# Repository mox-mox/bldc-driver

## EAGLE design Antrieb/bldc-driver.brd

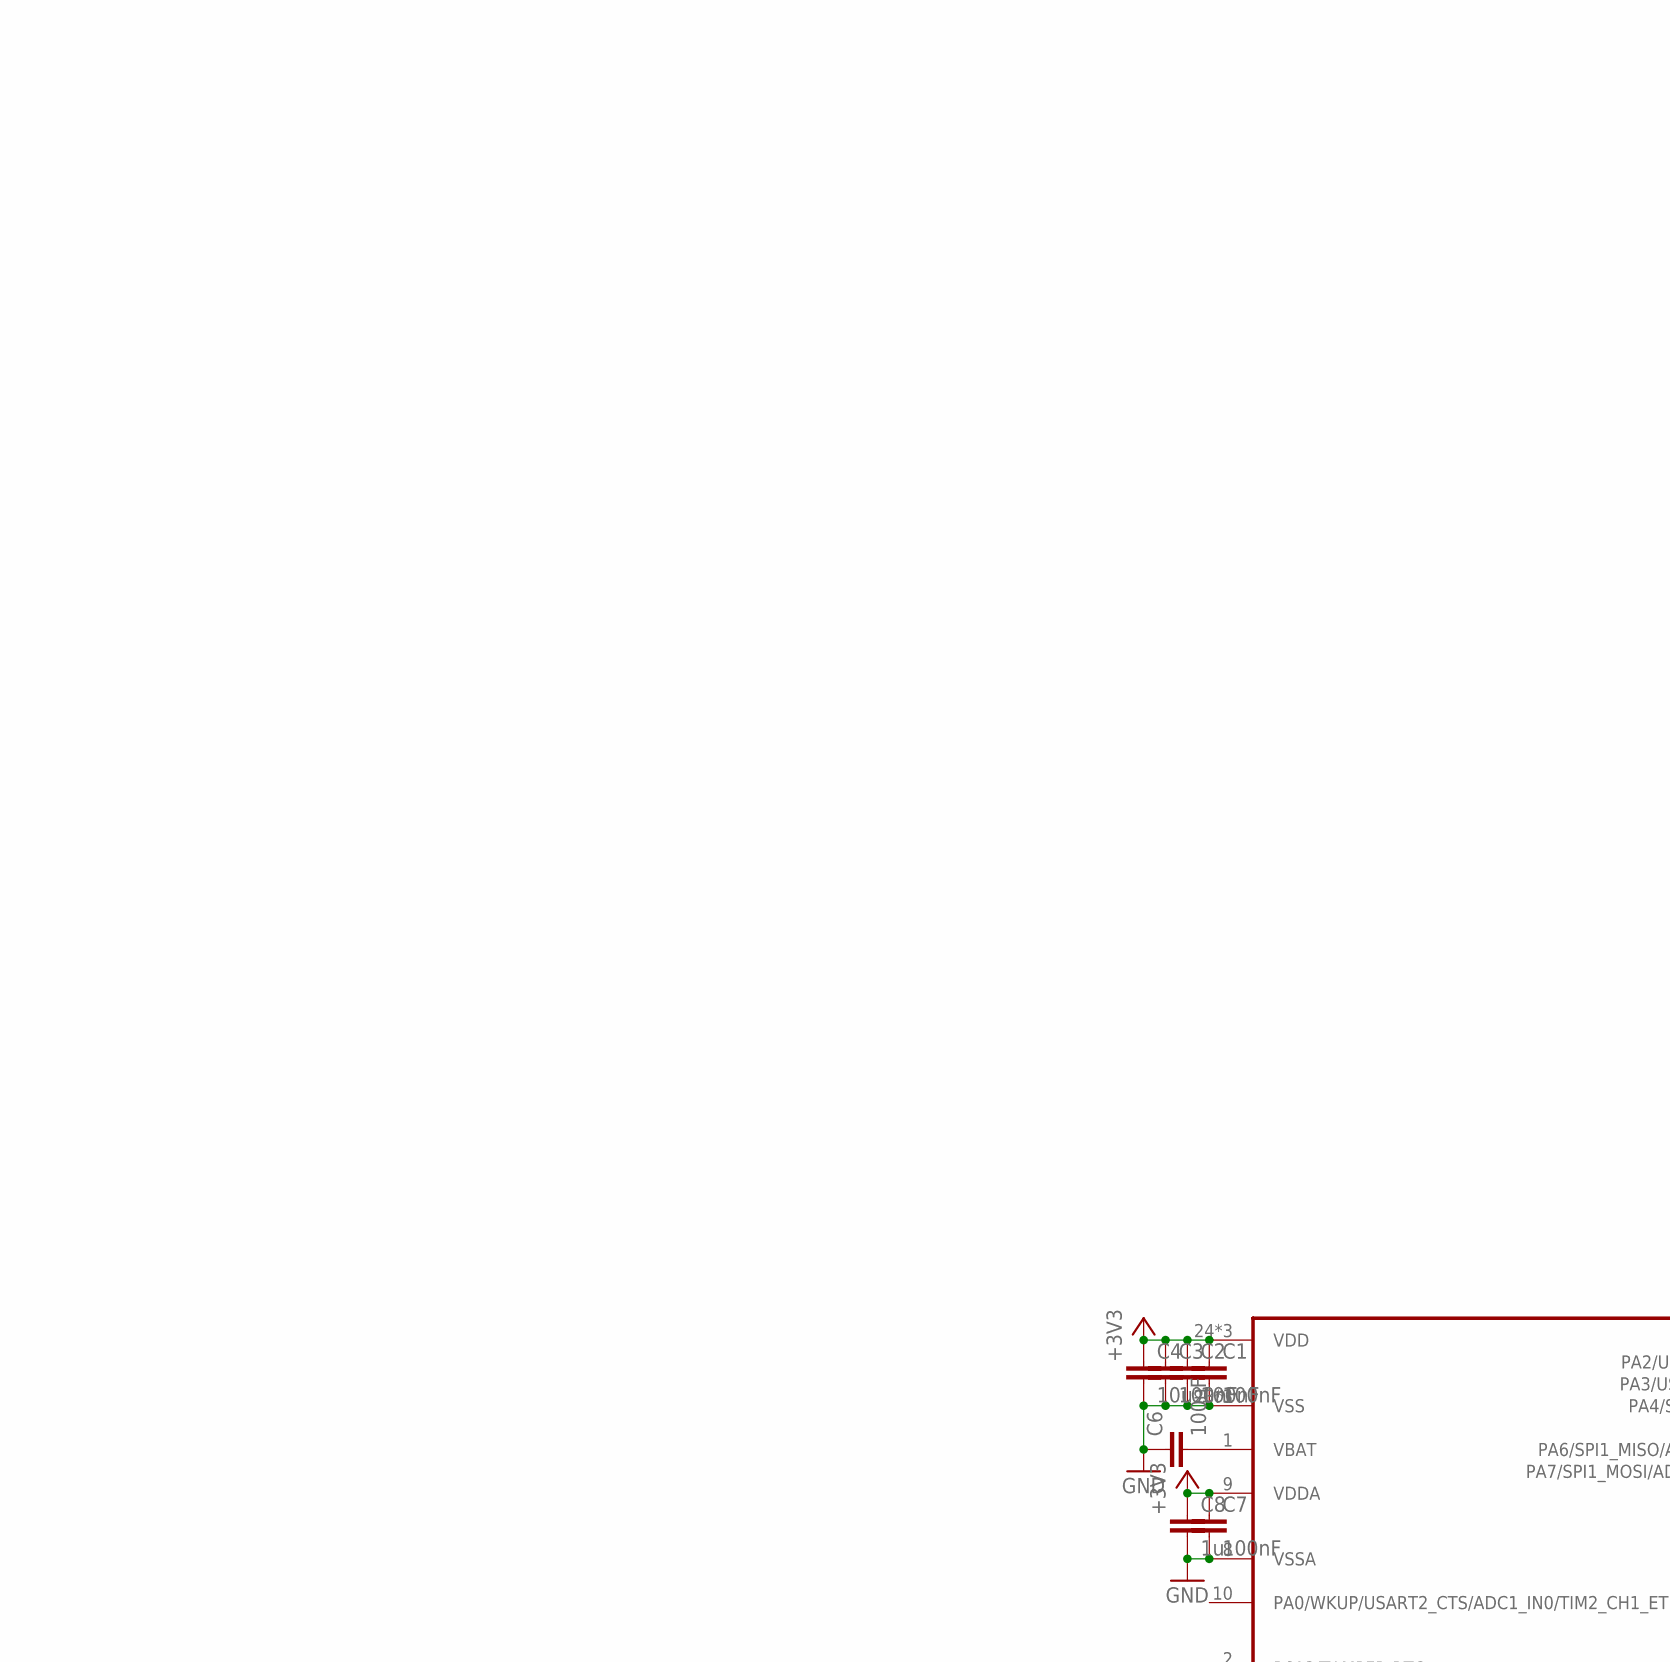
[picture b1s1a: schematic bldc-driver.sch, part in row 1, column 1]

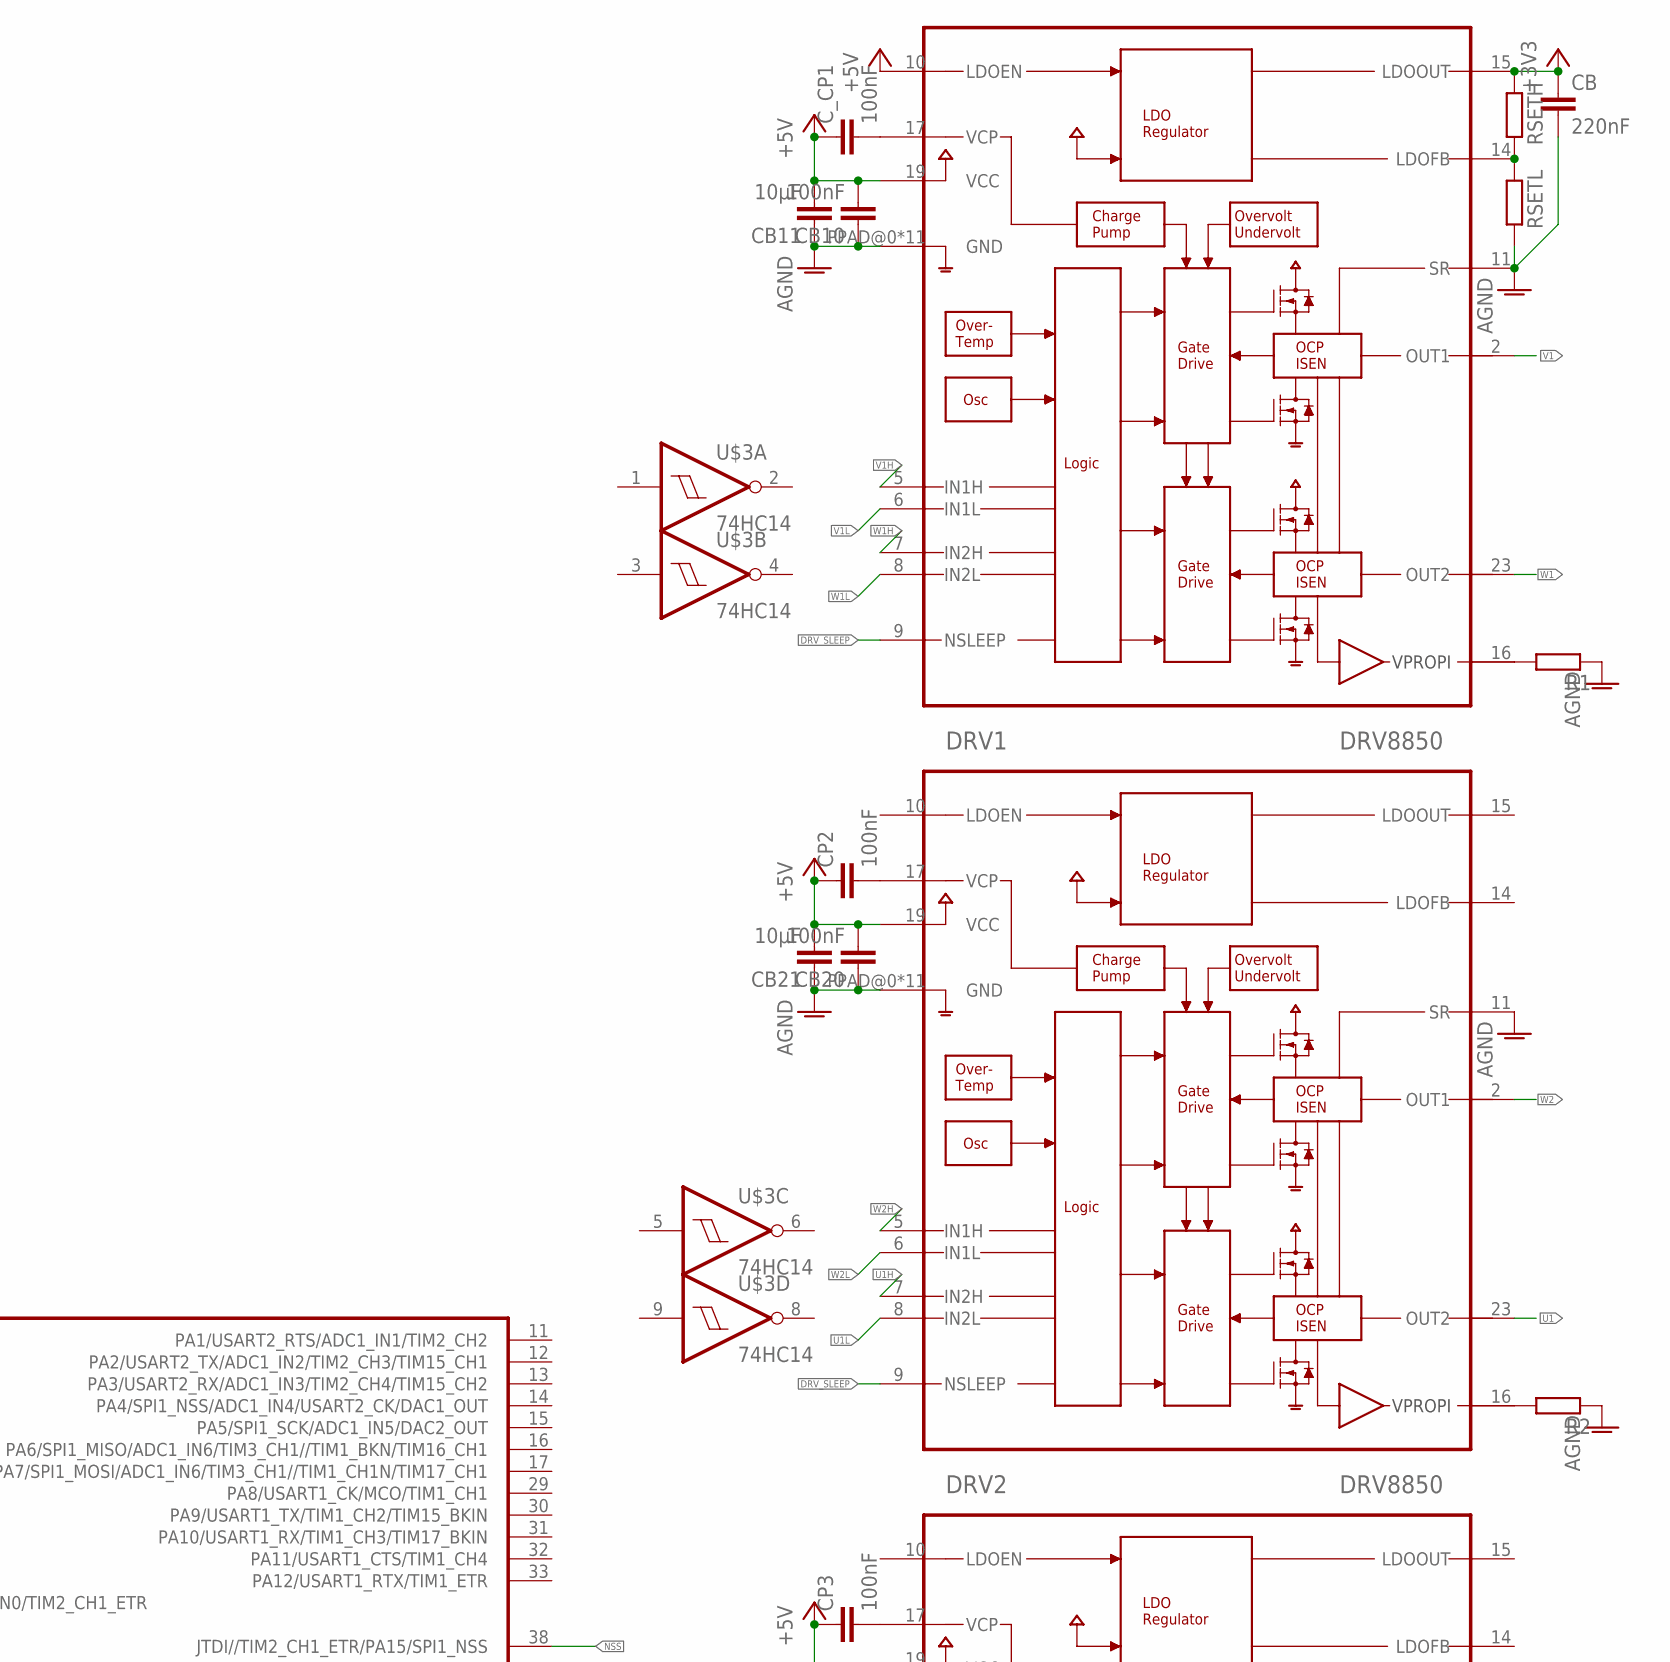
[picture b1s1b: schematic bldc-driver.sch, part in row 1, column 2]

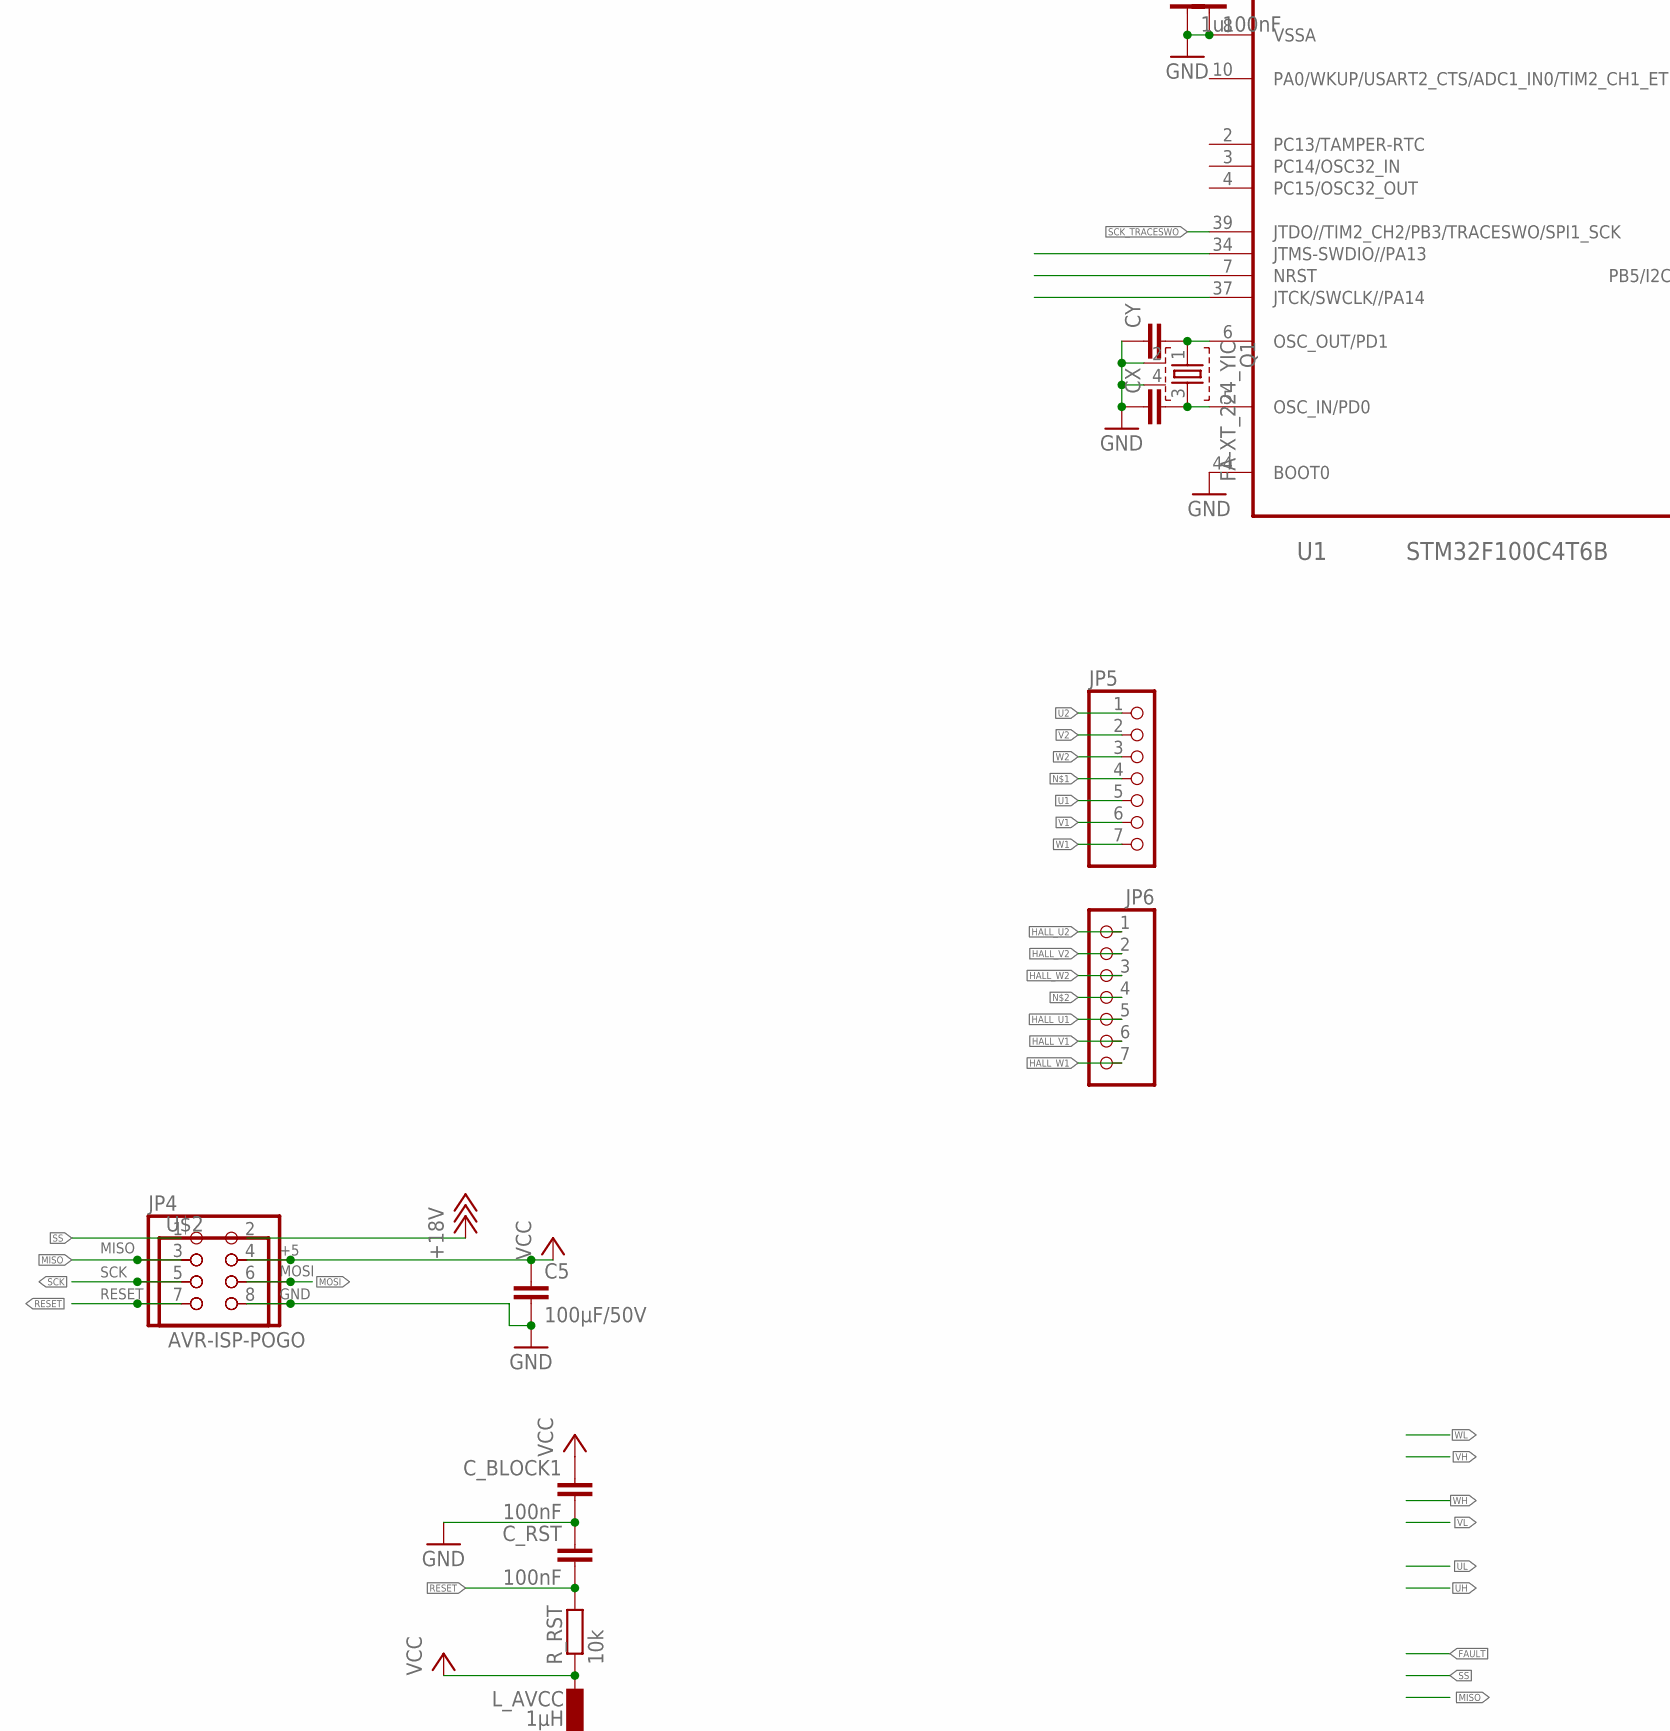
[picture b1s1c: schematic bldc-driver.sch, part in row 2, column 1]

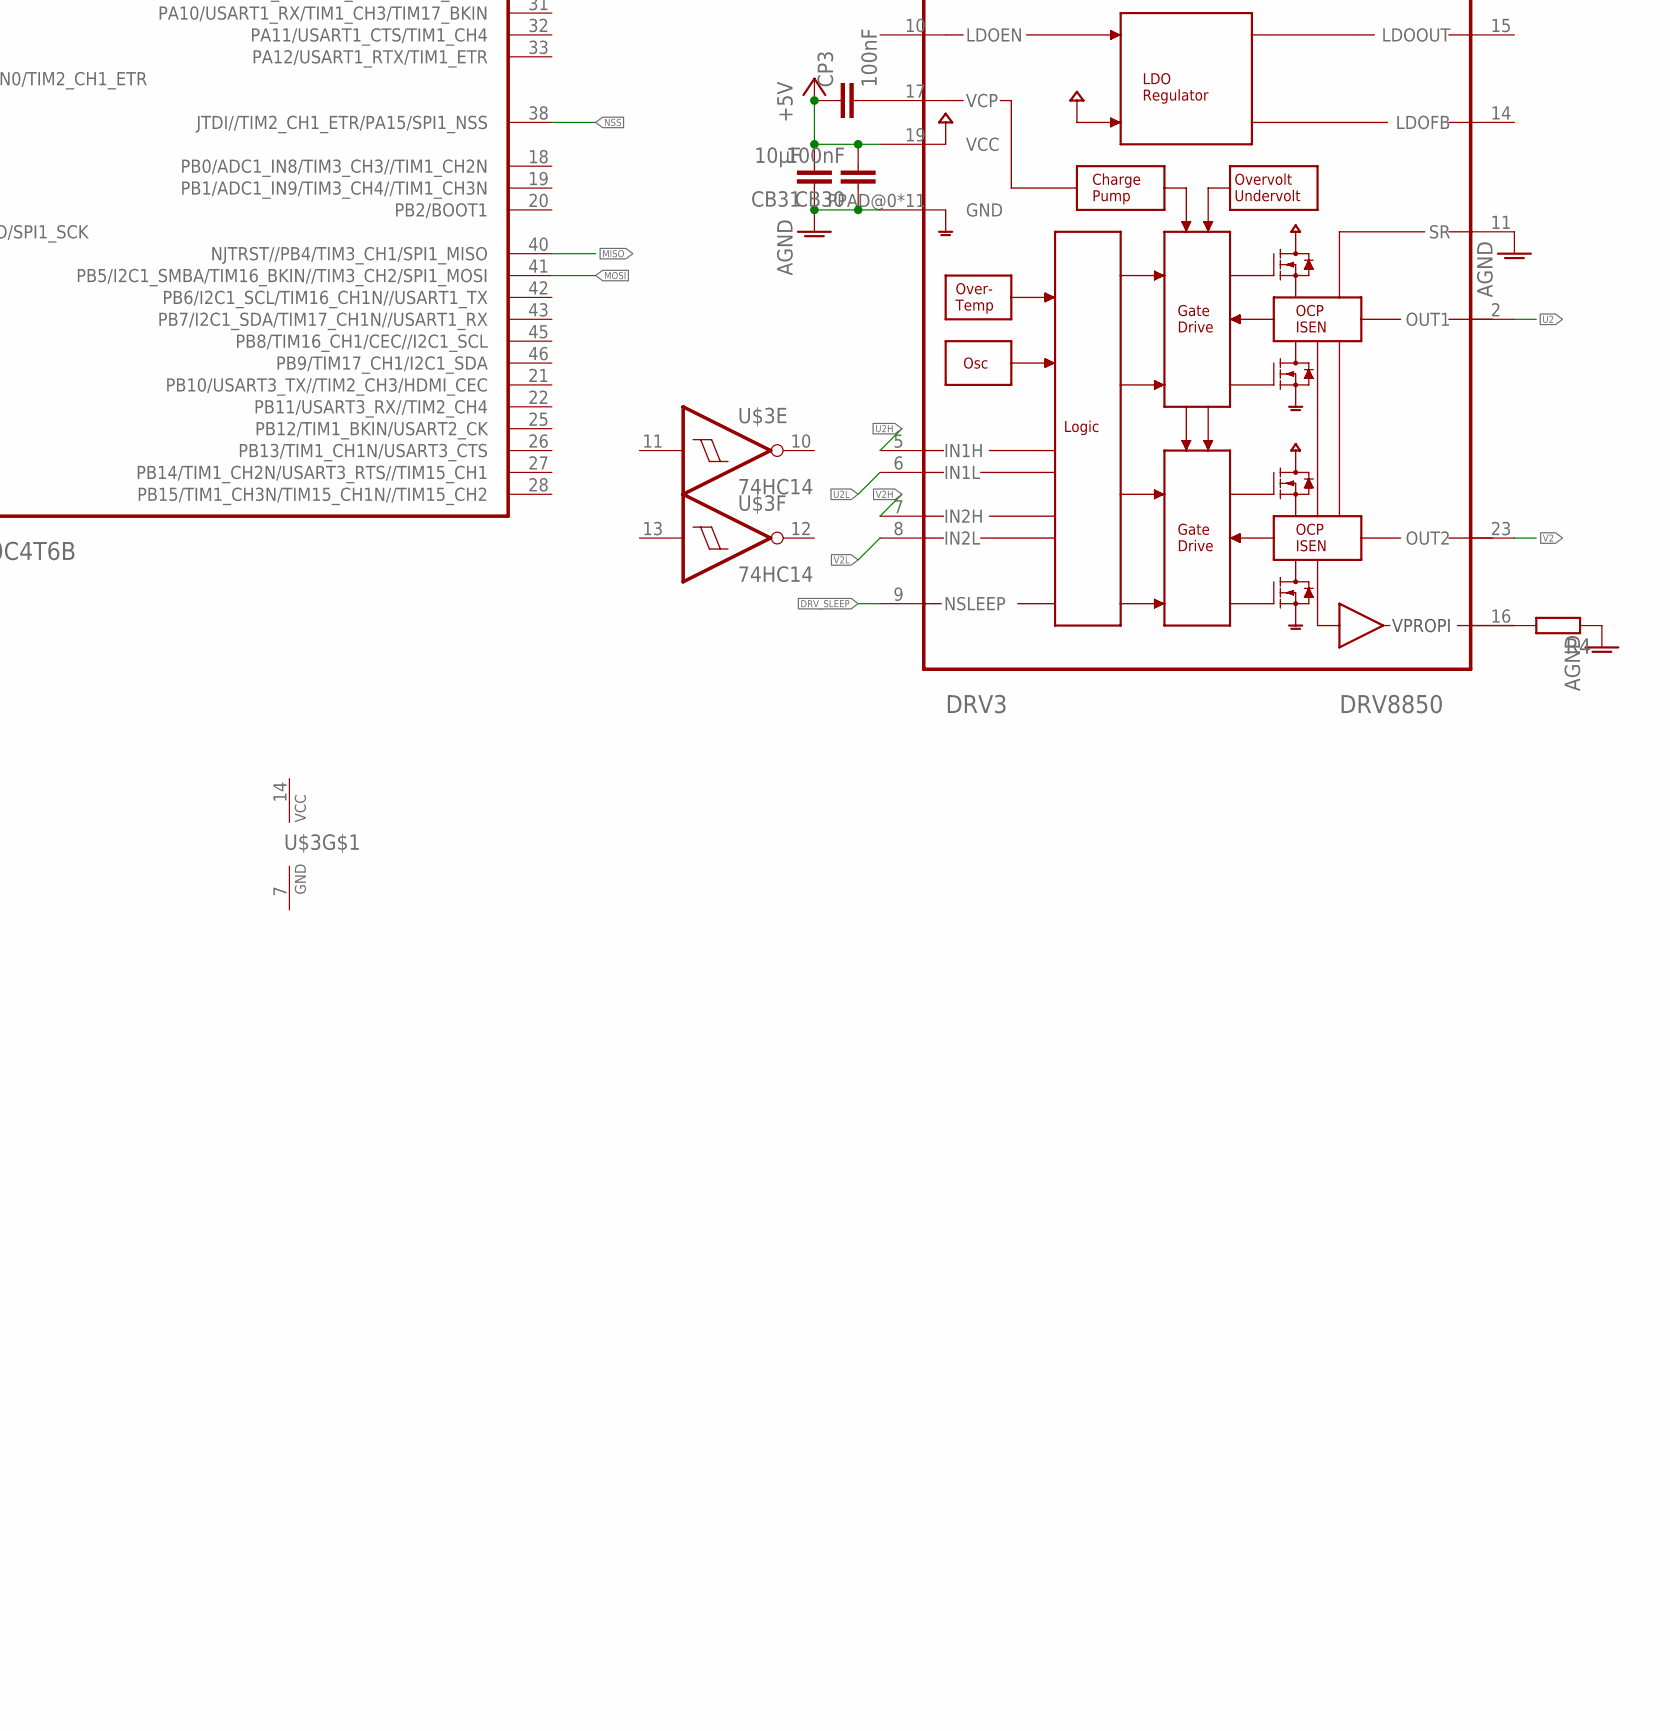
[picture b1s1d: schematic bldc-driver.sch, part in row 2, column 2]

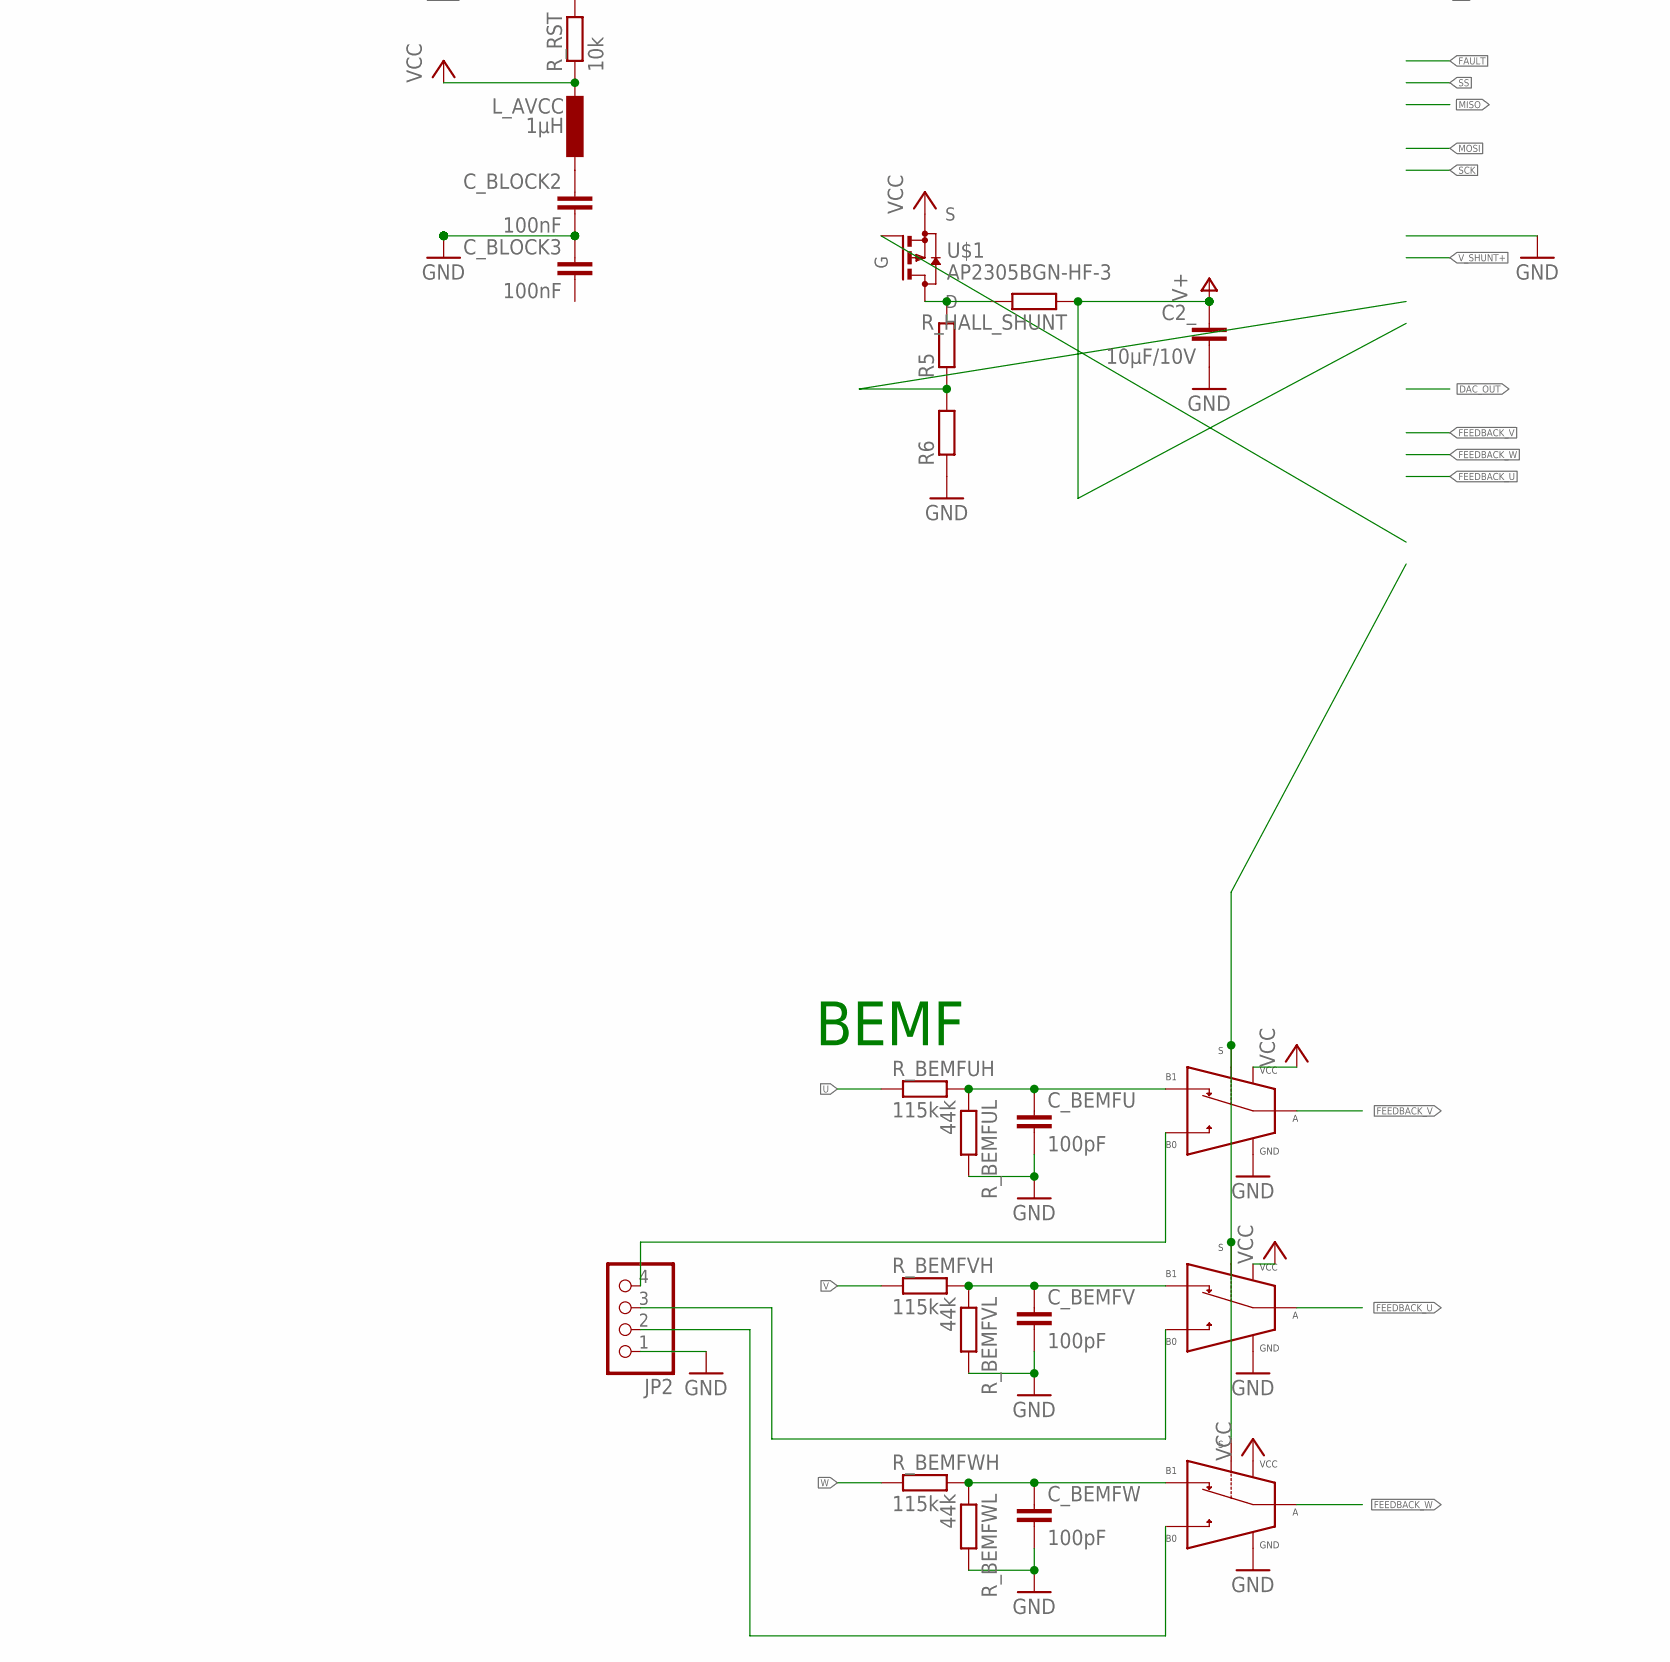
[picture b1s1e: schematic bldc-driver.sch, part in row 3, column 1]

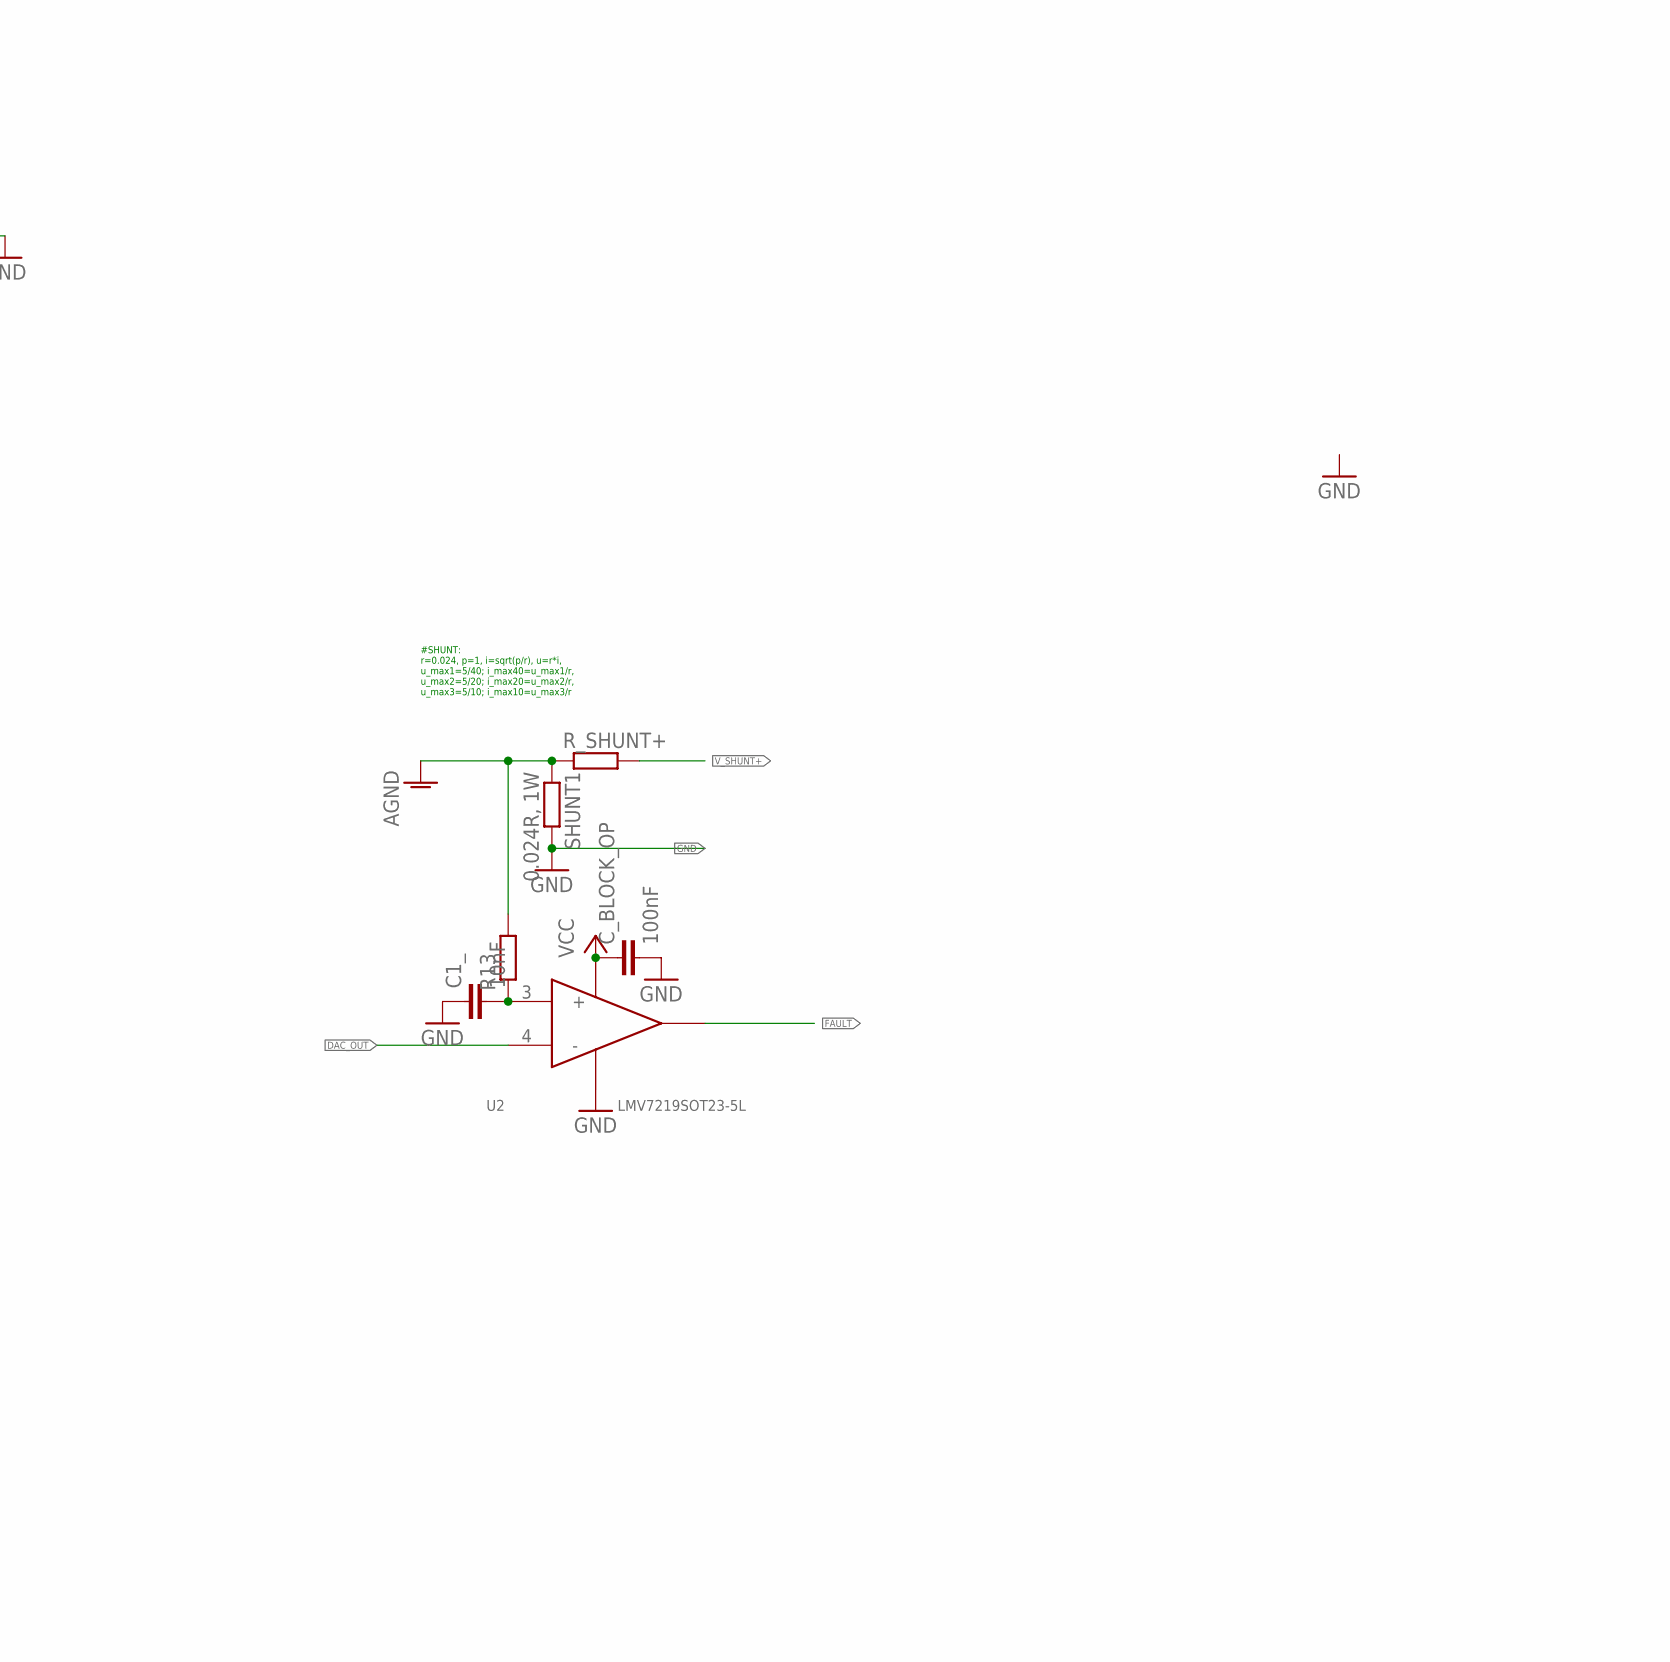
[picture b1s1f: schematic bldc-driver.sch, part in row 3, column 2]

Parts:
C1, C2, C3, C6, C7: 100nF; C0402
C1_: 10nF; C0402
C2_: 10µF/10V; C0603
C4: 10u; C0402
C5: 100µF/50V; C1206
C8: 1u; C0402
CB: 220nF; C0402
CB10, CB20, CB30: 100nF; C0402
CB11, CB21, CB31: 10µF; C0402
CP2, CP3: 100nF; C0402
CX: C-EUC0402; C0402
CY: C-EUC0402; C0402
C_BEMFU: 100pF; C0402
C_BEMFV: 100pF; C0402
C_BEMFW: 100pF; C0402
C_BLOCK1, C_BLOCK2, C_BLOCK3: 100nF; C0402
C_BLOCK_OP: 100nF; C0402
C_CP1: 100nF; C0402
C_RST: 100nF; C0402
DRV1, DRV2, DRV3: DRV8850RGY24_MOD; RGY.24_MOD
JP2: PINHD-1X4_2.54-SMD-90°; 1X04SMD/90
JP4: PINHD-2X4_2.00_3+5_MOD; 2X04_MOD
JP5, JP6: PINHD-1X7_2.54-SMD-90°; 1X07SMD/90
L_AVCC: 1µH; L0603
MUL_U: NC7SB3157P6XSC70-6; SC70-6
MUL_V: NC7SB3157P6XSC70-6; SC70-6
MUL_W: NC7SB3157P6XSC70-6; SC70-6
Q1: FA-XT_224_YIC; XT_224
R1, R2, R4, R5, R6, R13: R-EU_R0402; R0402
RSETH: R-EU_R0402; R0402
RSETL: R-EU_R0402; R0402
R_BEMFUH: 115k; R0402
R_BEMFUL: 44k; R0402
R_BEMFVH: 115k; R0402
R_BEMFVL: 44k; R0402
R_BEMFWH: 115k; R0402
R_BEMFWL: 44k; R0402
R_HALL_SHUNT: R-EU_R0402; R0402
R_RST: 10k; R0402
R_SHUNT+: R-EU_R0402; R0402
SHUNT1: 0.024R, 1W; R2512
U1: STM32F100C4T6B; QFP50P900X900X160-48N
U2: LMV7219SOT23-5L; SOT23-5L
U$1: AP2305BGN-HF-3; SOT23
U$2: AVR-ISP-POGO; ISP-THT-SMALL-POGOPIN
U$3: 74HC14; SSOP14

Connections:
+3V3: C1.1, C2.1, C3.1, C4.1, C7.1, C8.1, CB.1, DRV1.15 (LDOOUT), RSETH.1, U1.9 (VDDA), U1.24 (VDD), U1.36 (VDD), U1.48 (VDD)
+5V: CB10.2, CB11.2, CB20.2, CB21.2, CB30.2, CB31.2, CP2.1, CP3.1, C_CP1.1, DRV1.10 (LDOEN), DRV1.19 (VCC), DRV2.19 (VCC), DRV3.19 (VCC)
+18V: JP4.2
AGND: CB.2, CB10.1, CB11.1, CB20.1, CB21.1, CB30.1, CB31.1, DRV1.11 (SR), DRV1.PPAD@0 (GND), DRV1.PPAD@1 (GND), DRV1.PPAD@2 (GND), DRV1.PPAD@3 (GND), DRV1.PPAD@4 (GND), DRV1.PPAD@5 (GND), DRV1.PPAD@6 (GND), DRV1.PPAD@7 (GND), DRV1.PPAD@8 (GND), DRV1.PPAD@9 (GND), DRV1.PPAD@10 (GND), DRV2.11 (SR), DRV2.PPAD@0 (GND), DRV2.PPAD@1 (GND), DRV2.PPAD@2 (GND), DRV2.PPAD@3 (GND), DRV2.PPAD@4 (GND), DRV2.PPAD@5 (GND), DRV2.PPAD@6 (GND), DRV2.PPAD@7 (GND), DRV2.PPAD@8 (GND), DRV2.PPAD@9 (GND), DRV2.PPAD@10 (GND), DRV3.11 (SR), DRV3.PPAD@0 (GND), DRV3.PPAD@1 (GND), DRV3.PPAD@2 (GND), DRV3.PPAD@3 (GND), DRV3.PPAD@4 (GND), DRV3.PPAD@5 (GND), DRV3.PPAD@6 (GND), DRV3.PPAD@7 (GND), DRV3.PPAD@8 (GND), DRV3.PPAD@9 (GND), DRV3.PPAD@10 (GND), R1.1, R2.1, R4.1, R13.2, RSETL.2, R_SHUNT+.1, SHUNT1.1
AVCC: C_BLOCK2.1, L_AVCC.2
BEMF_U: C_BEMFU.1, MUL_U.1 (B1), R_BEMFUH.2, R_BEMFUL.1
BEMF_V: C_BEMFV.1, MUL_V.1 (B1), R_BEMFVH.2, R_BEMFVL.1
BEMF_W: C_BEMFW.1, MUL_W.1 (B1), R_BEMFWH.2, R_BEMFWL.1
DAC_OUT: U2.4 (-)
DRV_SLEEP: DRV1.9 (NSLEEP), DRV2.9 (NSLEEP), DRV3.9 (NSLEEP)
FAULT: U2.1 (OUT)
FEEDBACK_U: MUL_V.4 (A)
FEEDBACK_V: MUL_U.4 (A)
FEEDBACK_W: MUL_W.4 (A)
GND: C1.2, C1_.1, C2.2, C2_.2, C3.2, C4.2, C5.2, C6.1, C7.2, C8.2, CX.1, CY.1, C_BEMFU.2, C_BEMFV.2, C_BEMFW.2, C_BLOCK1.2, C_BLOCK2.2, C_BLOCK3.1, C_BLOCK_OP.2, C_RST.1, JP2.1, JP4.8, MUL_U.2 (GND), MUL_V.2 (GND), MUL_W.2 (GND), Q1.2, Q1.4, R6.1, R_BEMFUL.2, R_BEMFVL.2, R_BEMFWL.2, SHUNT1.2, U1.8 (VSSA), U1.23 (VSS), U1.35 (VSS), U1.44 (BOOT0), U1.47 (VSS), U2.2 (V-), U$2.6 (GND), U$3.7 (GND)
HALL_U: JP2.4, MUL_U.3 (B0)
HALL_U1: JP6.5
HALL_U2: JP6.1
HALL_V: JP2.3, MUL_V.3 (B0)
HALL_V1: JP6.6
HALL_V2: JP6.2
HALL_W: JP2.2, MUL_W.3 (B0)
HALL_W1: JP6.7
HALL_W2: JP6.3
MISO: JP4.3, U1.40 (NJTRST//PB4/TIM3_CH1/SPI1_MISO), U$2.1 (MISO)
MOSI: JP4.6, U1.41 (PB5/I2C1_SMBA/TIM16_BKIN//TIM3_CH2/SPI1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), U$2.4 (MOSI)
unnamed: C1_.2, R13.1, U2.3 (+)
unnamed: R5.1, R6.2
unnamed: R5.2, R_HALL_SHUNT.2, U$1.2 (D)
unnamed: C6.2, U1.1 (VBAT)
unnamed: DRV2.16 (VPROPI), R2.2
unnamed: C_CP1.2, DRV1.17 (VCP)
unnamed: CP3.2, DRV3.17 (VCP)
unnamed: DRV1.16 (VPROPI), R1.2
unnamed: DRV3.16 (VPROPI), R4.2
unnamed: CP2.2, DRV2.17 (VCP)
unnamed: DRV1.14 (LDOFB), RSETH.2, RSETL.1
NSS: U1.38 (JTDI//TIM2_CH1_ETR/PA15/SPI1_NSS)
RESET: C_RST.2, JP4.7, R_RST.2, U$2.5 (RESET)
SCK: JP4.5, U$2.3 (SCK)
SCK_TRACESWO: U1.39 (JTDO//TIM2_CH2/PB3/TRACESWO/SPI1_SCK)
SS: JP4.1
SWITCH_BEMF_HALL: MUL_U.6 (S), MUL_V.6 (S), MUL_W.6 (S)
U: R_BEMFUH.1
U1: DRV2.23 (OUT2), JP5.5
U1H: DRV2.7 (IN2H)
U1L: DRV2.8 (IN2L)
U2: DRV3.2 (OUT1), JP5.1
U2H: DRV3.5 (IN1H)
U2L: DRV3.6 (IN1L)
V: R_BEMFVH.1
V1: DRV1.2 (OUT1), JP5.6
V1H: DRV1.5 (IN1H)
V1L: DRV1.6 (IN1L)
V2: DRV3.23 (OUT2), JP5.2
V2H: DRV3.7 (IN2H)
V2L: DRV3.8 (IN2L)
V+: C2_.1, R_HALL_SHUNT.1
VCC: C5.1, C_BLOCK1.1, C_BLOCK_OP.1, JP4.4, L_AVCC.1, MUL_U.5 (VCC), MUL_V.5 (VCC), MUL_W.5 (VCC), R_RST.1, U2.5 (V+), U$1.3 (S), U$2.2 (+5), U$3.14 (VCC)
V_SHUNT+: R_SHUNT+.2
W: R_BEMFWH.1
W1: DRV1.23 (OUT2), JP5.7
W1H: DRV1.7 (IN2H)
W1L: DRV1.8 (IN2L)
W2: DRV2.2 (OUT1), JP5.3
W2H: DRV2.5 (IN1H)
W2L: DRV2.6 (IN1L)
XTAL1: CY.2, Q1.1, U1.6 (OSC_OUT/PD1)
XTAL2: CX.2, Q1.3, U1.5 (OSC_IN/PD0)

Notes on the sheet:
BEMF
#SHUNT: r=0.024, p=1, i=sqrt(p/r), u=r*i, u_max1=5/40; i_max40=u_max1/r, u_max2=5/20; i_max20=u_max2/r, u_max3=5/10; i_max10=u_max3/r

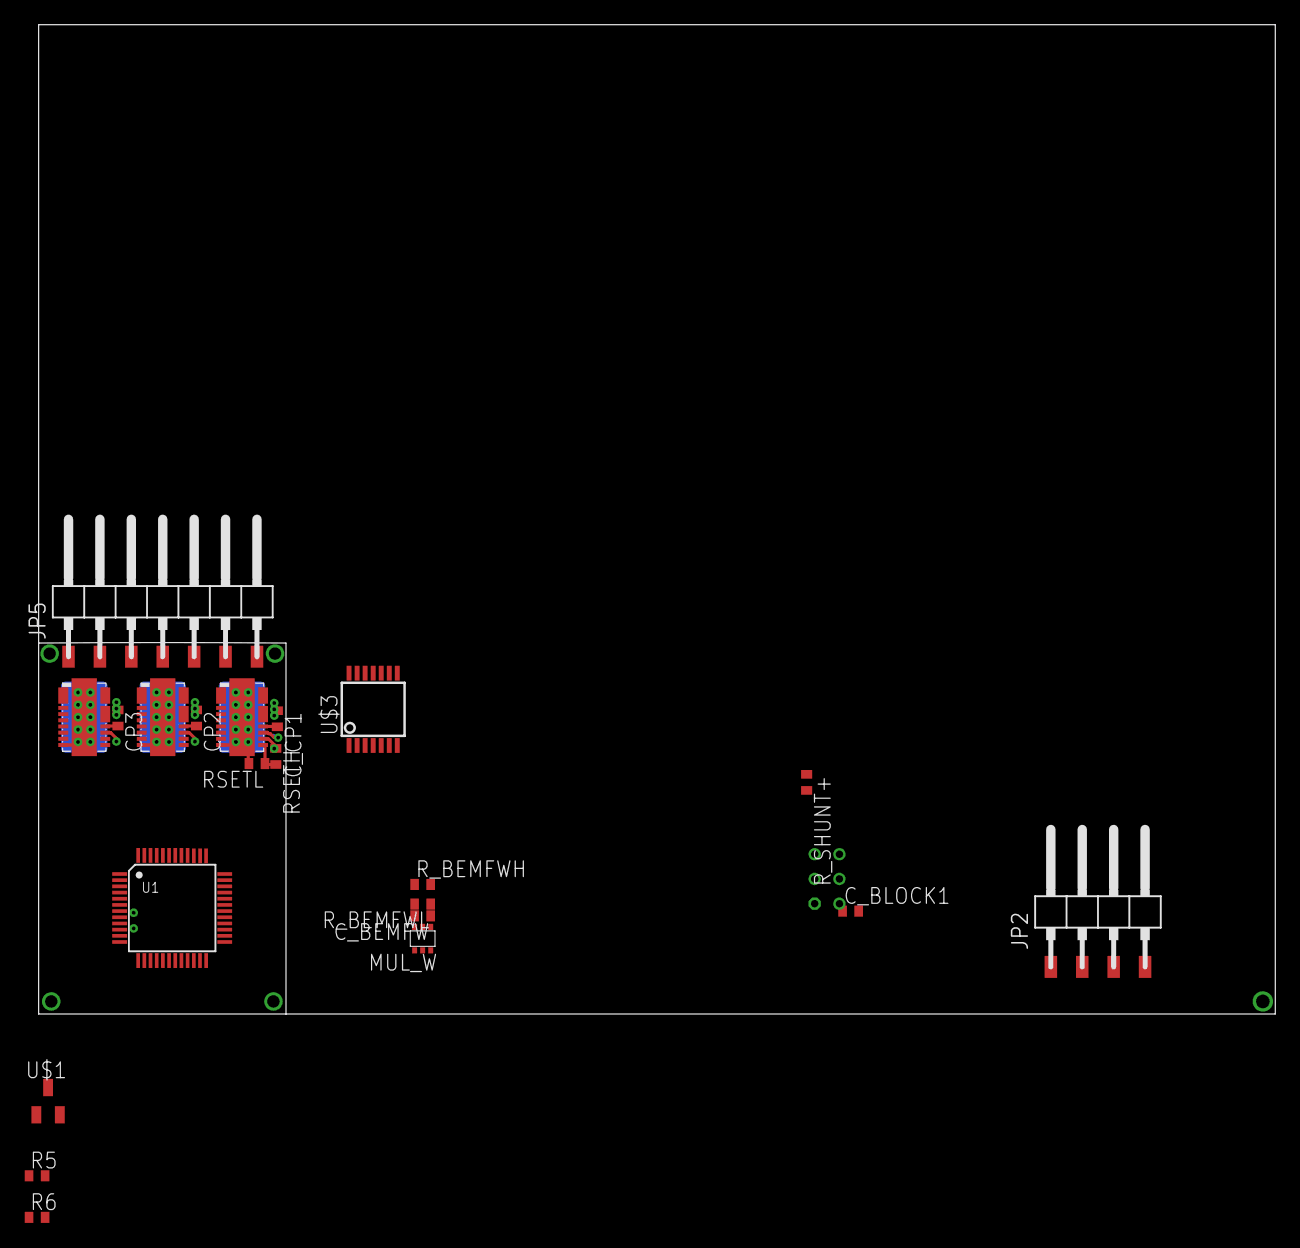
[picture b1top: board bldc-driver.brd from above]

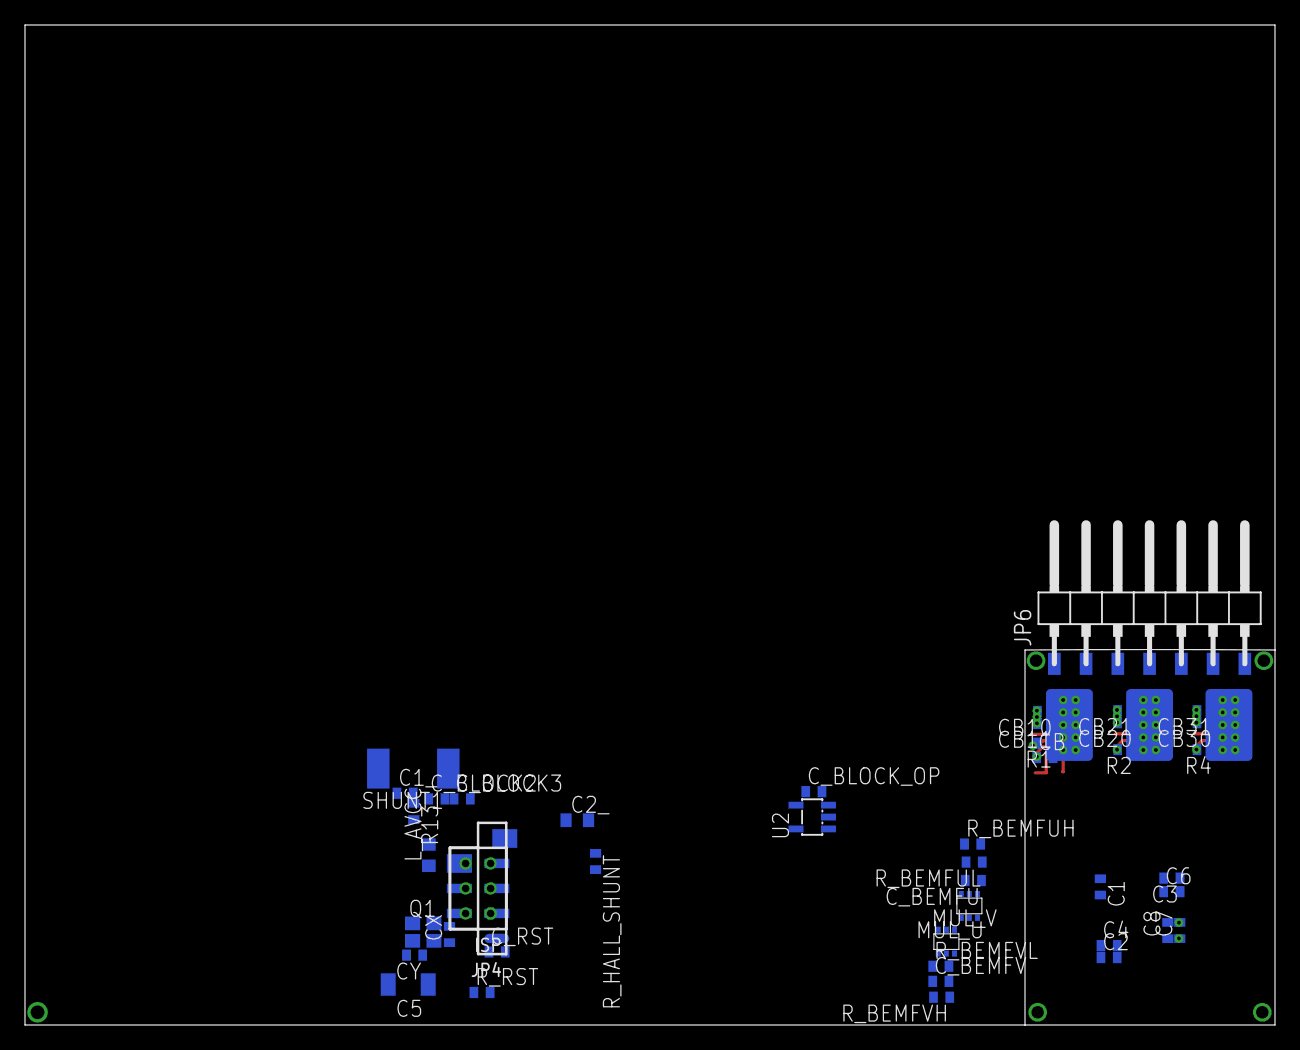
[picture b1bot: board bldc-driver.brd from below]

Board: 2 copper layers, 100.0 x 80.0 mm, 65 parts (44 on the bottom side), 38 nets.
